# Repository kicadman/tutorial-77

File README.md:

# tutorial-77 
このプロジェクトは[入門実習テキスト「KiCad Basics for 10.0」](https://kosakalab.booth.pm/items/8151716)付録本「KiCad-GitHub Basic」用の教材です。

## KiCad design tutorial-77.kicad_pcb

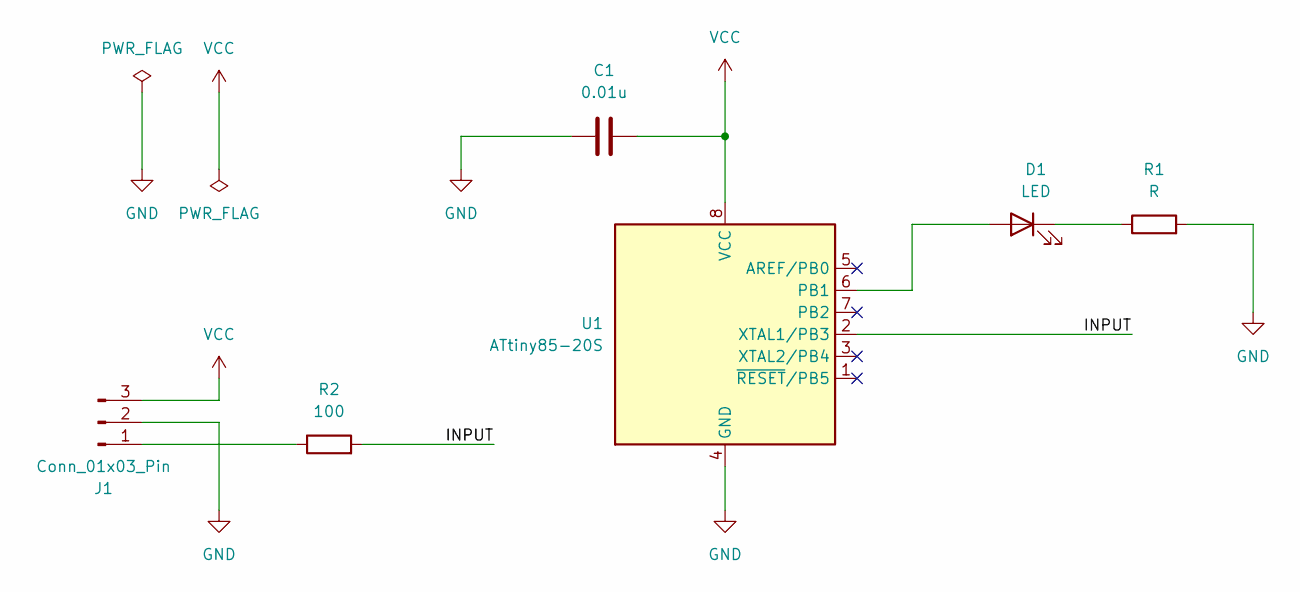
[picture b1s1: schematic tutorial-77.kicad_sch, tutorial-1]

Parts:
C1: 0.01u; C_0603_1608Metric_Pad1.08x0.95mm_HandSolder
D1: LED; LED_0603_1608Metric_Pad1.05x0.95mm_HandSolder
J1: Conn_01x03_Pin; PinHeader_1x03_P2.54mm_Vertical
R1: R; R_0603_1608Metric_Pad0.98x0.95mm_HandSolder
R2: 100; R_0603_1608Metric_Pad0.98x0.95mm_HandSolder
U1: ATtiny85-20S; SOIC-8_5.3x5.3mm_P1.27mm

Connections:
/INPUT: R2.2, U1.2 (XTAL1/PB3)
GND: C1.1, J1.2, R1.2, U1.4 (GND)
unnamed: D1.2 (A), U1.6 (PB1)
unnamed: D1.1 (K), R1.1
unnamed: J1.1, R2.1
VCC: C1.2, J1.3, U1.8 (VCC)

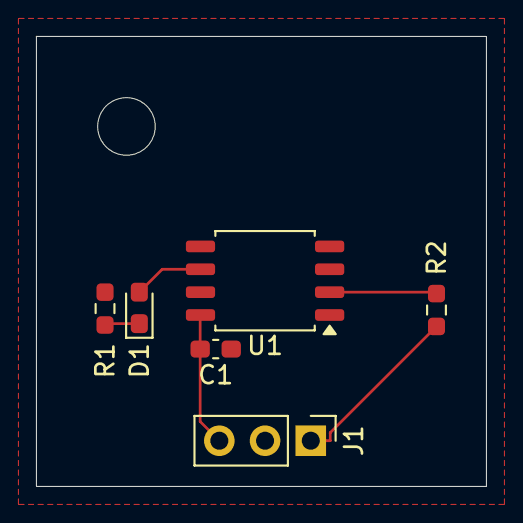
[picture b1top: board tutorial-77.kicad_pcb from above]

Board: 2 copper layers, 25.0 x 25.0 mm, 7 parts (0 on the bottom side), 6 nets.

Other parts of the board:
MH1: MountingHole_3.2mm_M3

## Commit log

2026-06-11 Update README.md(v.1.0.0)
    プロジェクトの説明を加えた
2026-06-13 plan-b 部品配置変更
2026-06-13 plan-a autorouter
    自動配線
2026-06-13 plan-b adjust parts position
2026-06-13 Lastest plan-a
2026-06-13 plan-b 最終版
